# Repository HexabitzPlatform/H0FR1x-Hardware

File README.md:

# H0FR1x-Hardware
Hexabitz 230V/10A(RMS) SPDT Relay Module Hardware Design

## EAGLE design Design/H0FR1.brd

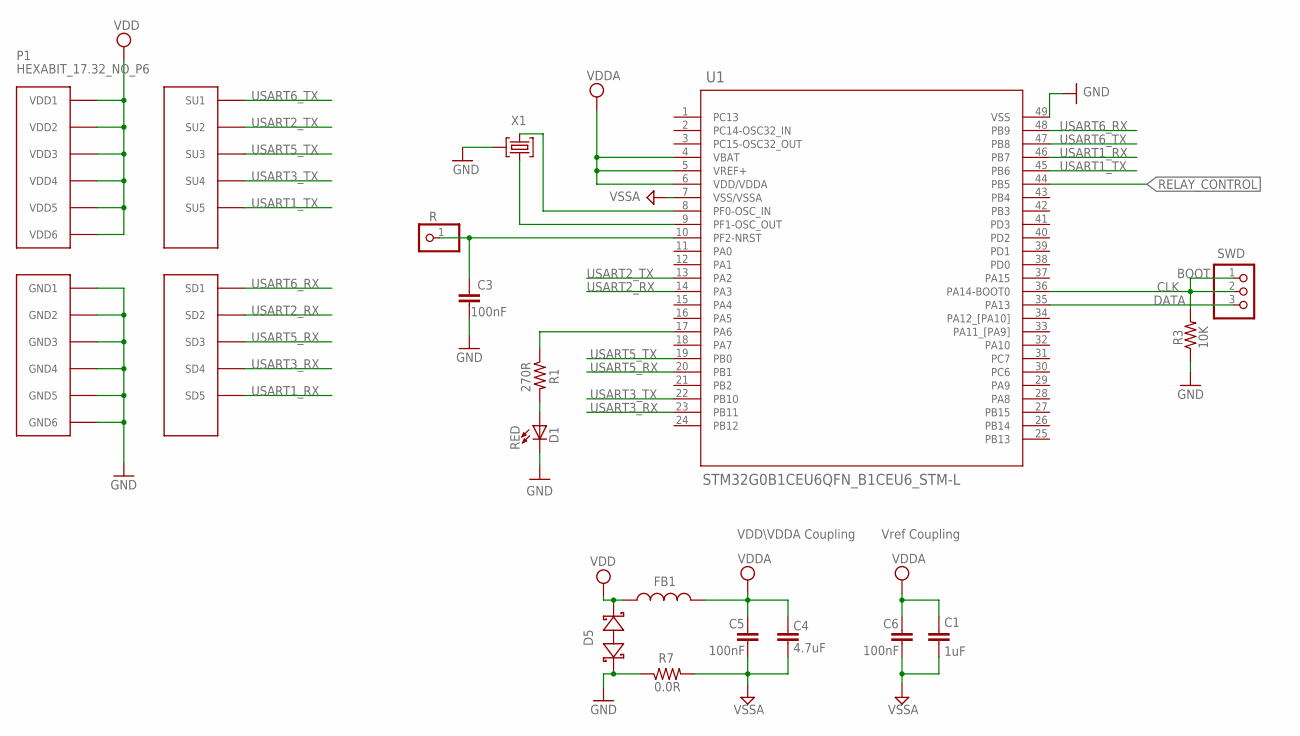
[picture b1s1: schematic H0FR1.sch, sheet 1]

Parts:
C1: 1uF; C-0805
C3, C5, C6: 100nF; C-0603
C4: 4.7uF; C-0805
D1: RED; VLMS1300-GS08; MPN VLMS1300-GS08
D5: BOURNS_CDSOD323-T03SCBOURNS_CDSOD323-T03SC_0_0; BOURNS_CDSOD323-T03SC_0
FB1: FB-TDK_MMZ1608Y300B; FB-0603; MPN MMZ1608Y300B
P1: HEXABIT_17.32_NO_P6
R: R; 1X01
R1: 270R; R-0603
R3: 10K; R-0603
R7: 0.0R; R-0603; MPN RC0603JR-070RL
SWD: PINHD-1X3; 1X03
TRIMBLE-LOGO1: HEXA-LOGO
U1: STM32G0B1CEU6QFN_B1CEU6_STM-L; QFN_B1CEU6_STM-L
X1: XTALL_CSTCE8M00G52

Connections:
CLK: R3.2, SWD.1, SWD.2, U1.36 (PA14-BOOT0)
DATA: SWD.3, U1.35 (PA13)
GND: C3.2, D1.C, D5.1 (A), P1.PAD_PD7 (GND1), P1.PAD_PD8 (GND2), P1.PAD_PD9 (GND3), P1.PAD_PD10 (GND4), P1.PAD_PD11 (GND5), P1.PAD_PD12 (GND6), R3.1, R7.1, U1.49 (VSS), X1.P$2 (2); also elsewhere on the board
unnamed: D1.A, R1.2
unnamed: R1.1, U1.17 (PA6)
unnamed: C3.1, R.1, U1.10 (PF2-NRST)
unnamed: U1.9 (PF1-OSC_OUT), X1.P$1 (1)
unnamed: U1.8 (PF0-OSC_IN), X1.P$3 (3)
RELAY_CONTROL: U1.44 (PB5); also elsewhere on the board
USART1_RX: P1.PAD_PD5 (SD5), U1.46 (PB7)
USART1_TX: P1.PAD_PU5 (SU5), U1.45 (PB6)
USART2_RX: P1.PAD_PD2 (SD2), U1.14 (PA3)
USART2_TX: P1.PAD_PU2 (SU2), U1.13 (PA2)
USART3_RX: P1.PAD_PD4 (SD4), U1.23 (PB11)
USART3_TX: P1.PAD_PU4 (SU4), U1.22 (PB10)
USART5_RX: P1.PAD_PD3 (SD3), U1.20 (PB1)
USART5_TX: P1.PAD_PU3 (SU3), U1.19 (PB0)
USART6_RX: P1.PAD_PD1 (SD1), U1.48 (PB9)
USART6_TX: P1.PAD_PU1 (SU1), U1.47 (PB8)
VDD: D5.2 (C), FB1.2, P1.PAD_PU7 (VDD1), P1.PAD_PU8 (VDD2), P1.PAD_PU9 (VDD3), P1.PAD_PU10 (VDD4), P1.PAD_PU11 (VDD5), P1.PAD_PU12 (VDD6); also elsewhere on the board
VDDA: C1.1, C4.1, C5.1, C6.1, FB1.1, U1.4 (VBAT), U1.5 (VREF+), U1.6 (VDD/VDDA)
VSSA: C1.2, C4.2, C5.2, C6.2, R7.2, U1.7 (VSS/VSSA)

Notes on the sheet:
Vref Coupling
VDD\VDDA Coupling
BOOT

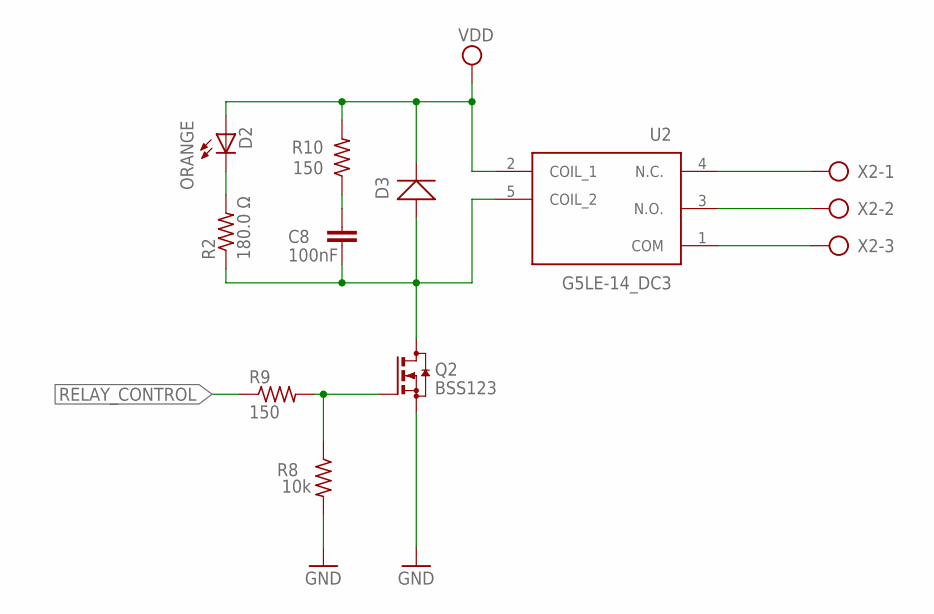
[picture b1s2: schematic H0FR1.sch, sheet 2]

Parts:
C8: 100nF; C-0603; TOLERANCE 10%; VOLTAGE_RATING 10V; MPN C0603C104K8RACTU
D2: orange; VLMS1300-GS08; MPN VLMY1300-GS08
D3: 40V 300MA; SOD-323
Q2: BSS123; SOT23
R2: 180.0 Ω; R-0603; TOLERANCE ±5%; MPN ERJ-3GEYJ181V
R8: 10k; R-0603; TOLERANCE 5%; MPN RC0603JR-07680KL
R9: 150; R-0603; TOLERANCE ±5%; MPN CRCW06031K00JNEA
R10: 150; R-0603; TOLERANCE 5%; MPN RC0603JR-07680KL
U2: G5LE-14_DC3; G5LE-14_SPDT
X2: AK300/3

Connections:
COM: U2.1 (COM), X2.3
GND: Q2.2 (S), R8.2; also elsewhere on the board
unnamed: C8.2, D3.+, Q2.3 (D), R2.1, U2.5 (COIL_2)
unnamed: D2.C, R2.2
unnamed: Q2.1 (G), R8.1, R9.2
unnamed: C8.1, R10.1
NC: U2.4 (N.C.), X2.1
NO: U2.3 (N.O.), X2.2
RELAY_CONTROL: R9.1; also elsewhere on the board
VDD: D2.A, D3.-, R10.2, U2.2 (COIL_1); also elsewhere on the board

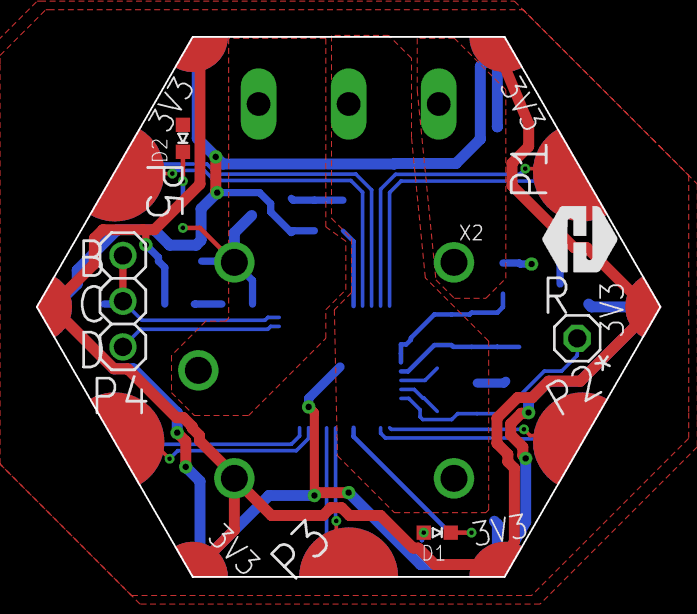
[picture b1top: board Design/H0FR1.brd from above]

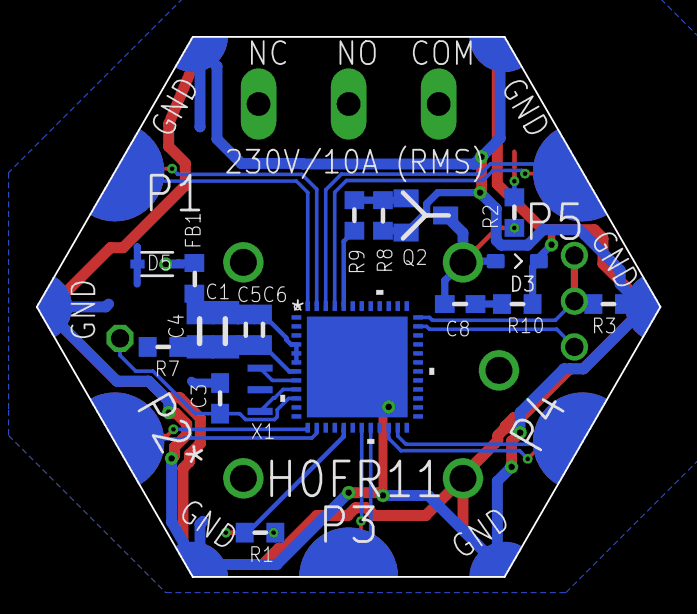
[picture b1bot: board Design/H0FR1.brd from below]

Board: 2 copper layers, 34.6 x 30.0 mm, 27 parts (19 on the bottom side), 29 nets.

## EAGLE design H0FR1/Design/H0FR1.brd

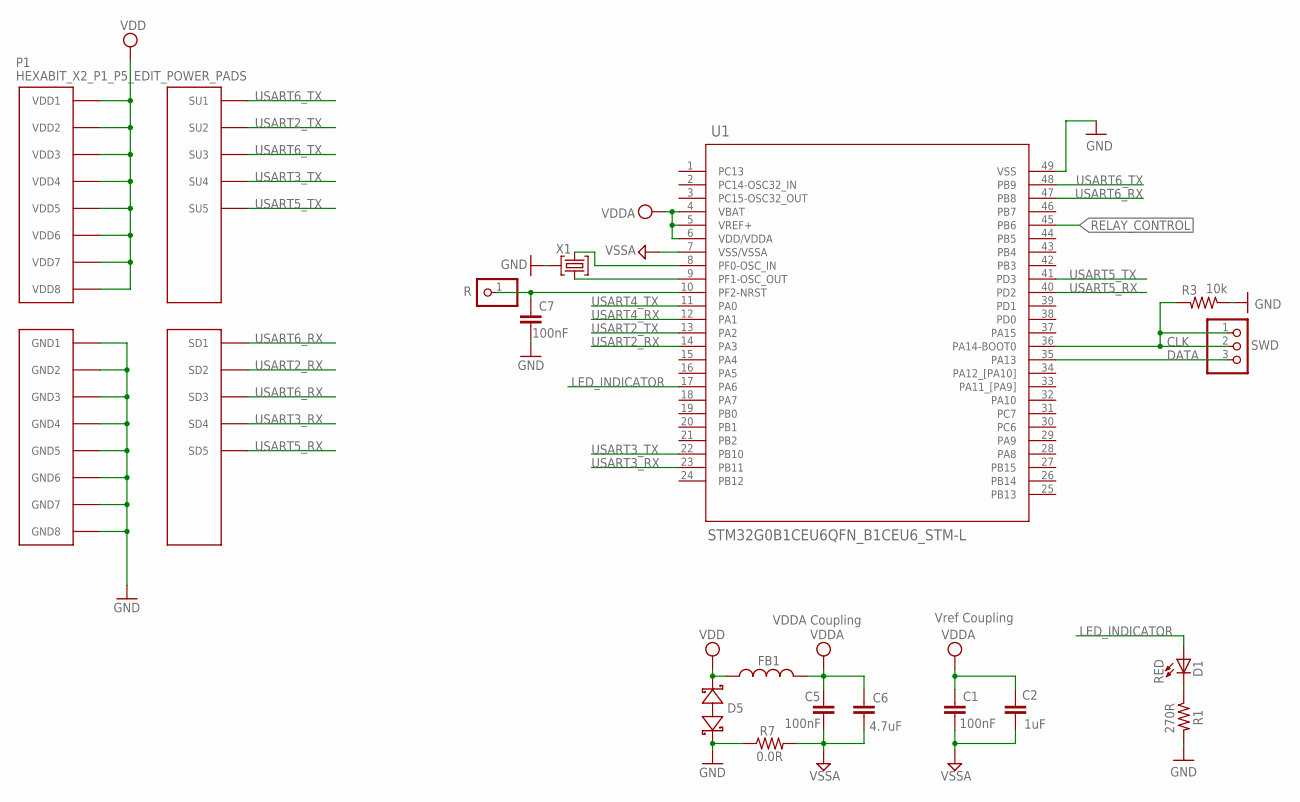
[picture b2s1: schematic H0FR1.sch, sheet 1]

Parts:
C1: 100nF; C-0603; TOLERANCE 10%; VOLTAGE_RATING 10V; MPN C0603C104K8RACTU
C2: 1uF; C-0805; TOLERANCE 10%; VOLTAGE_RATING 16V; MPN CC0805KKX7R7BB105
C5, C7: 100nF; C-0603
C6: 4.7uF; C-0805; TOLERANCE 10%; VOLTAGE_RATING 25V; MPN GRM21BC81E475KA12L
D1: RED; VLMS1300-GS08; MPN VLMS1300-GS08
D5: BOURNS_CDSOD323-T03SCBOURNS_CDSOD323-T03SC_0_0; BOURNS_CDSOD323-T03SC_0
FB1: FB-0603
P1: HEXABIT_X2_P1_P5_EDIT_POWER_PADS
R: R; 1X01
R1: 270R; R-0603
R3: 10k; R-0603; TOLERANCE 5%; MPN RC0603JR-0710KL
R7: 0.0R; R-0603
SWD: PINHD-1X3SWD; SWD
TRIMBLE-LOGO2: HEXA-LOGO
U1: STM32G0B1CEU6QFN_B1CEU6_STM-L; QFN_B1CEU6_STM-L
X1: XTALL_CSTCE8M00G52

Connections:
CLK: R3.2, SWD.1, SWD.2, U1.36 (PA14-BOOT0)
DATA: SWD.3, U1.35 (PA13)
GND: C7.2, D5.2 (C), P1.PAD_PD11 (GND1), P1.PAD_PD12 (GND2), P1.PAD_PD13 (GND3), P1.PAD_PD14 (GND4), P1.PAD_PD17 (GND5), P1.PAD_PD18 (GND6), P1.PAD_PD19 (GND7), P1.PAD_PD20 (GND8), R1.2, R3.1, R7.1, U1.49 (VSS), X1.P$2 (2); also elsewhere on the board
LED_INDICATOR: D1.A, U1.17 (PA6)
unnamed: D1.C, R1.1
unnamed: C7.1, R.1, U1.10 (PF2-NRST)
unnamed: U1.9 (PF1-OSC_OUT), X1.P$1 (1)
unnamed: U1.8 (PF0-OSC_IN), X1.P$3 (3)
RELAY_CONTROL: U1.45 (PB6); also elsewhere on the board
USART2_RX: P1.PAD_PD2 (SD2), U1.14 (PA3)
USART2_TX: P1.PAD_PU2 (SU2), U1.13 (PA2)
USART3_RX: P1.PAD_PD4 (SD4), U1.23 (PB11)
USART3_TX: P1.PAD_PU4 (SU4), U1.22 (PB10)
USART4_RX: U1.12 (PA1)
USART4_TX: U1.11 (PA0)
USART5_RX: P1.PAD_PD5 (SD5), U1.40 (PD2)
USART5_TX: P1.PAD_PU5 (SU5), U1.41 (PD3)
USART6_RX: P1.PAD_PD1 (SD1), P1.PAD_PD3 (SD3), U1.47 (PB8)
USART6_TX: P1.PAD_PU1 (SU1), P1.PAD_PU3 (SU3), U1.48 (PB9)
VDD: D5.1 (A), FB1.1, P1.PAD_PU11 (VDD1), P1.PAD_PU12 (VDD2), P1.PAD_PU13 (VDD3), P1.PAD_PU14 (VDD4), P1.PAD_PU17 (VDD5), P1.PAD_PU18 (VDD6), P1.PAD_PU19 (VDD7), P1.PAD_PU20 (VDD8); also elsewhere on the board
VDDA: C1.1, C2.1, C5.1, C6.1, FB1.2, U1.4 (VBAT), U1.5 (VREF+), U1.6 (VDD/VDDA)
VSSA: C1.2, C2.2, C5.2, C6.2, R7.2, U1.7 (VSS/VSSA)

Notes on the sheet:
Vref Coupling
VDDA Coupling

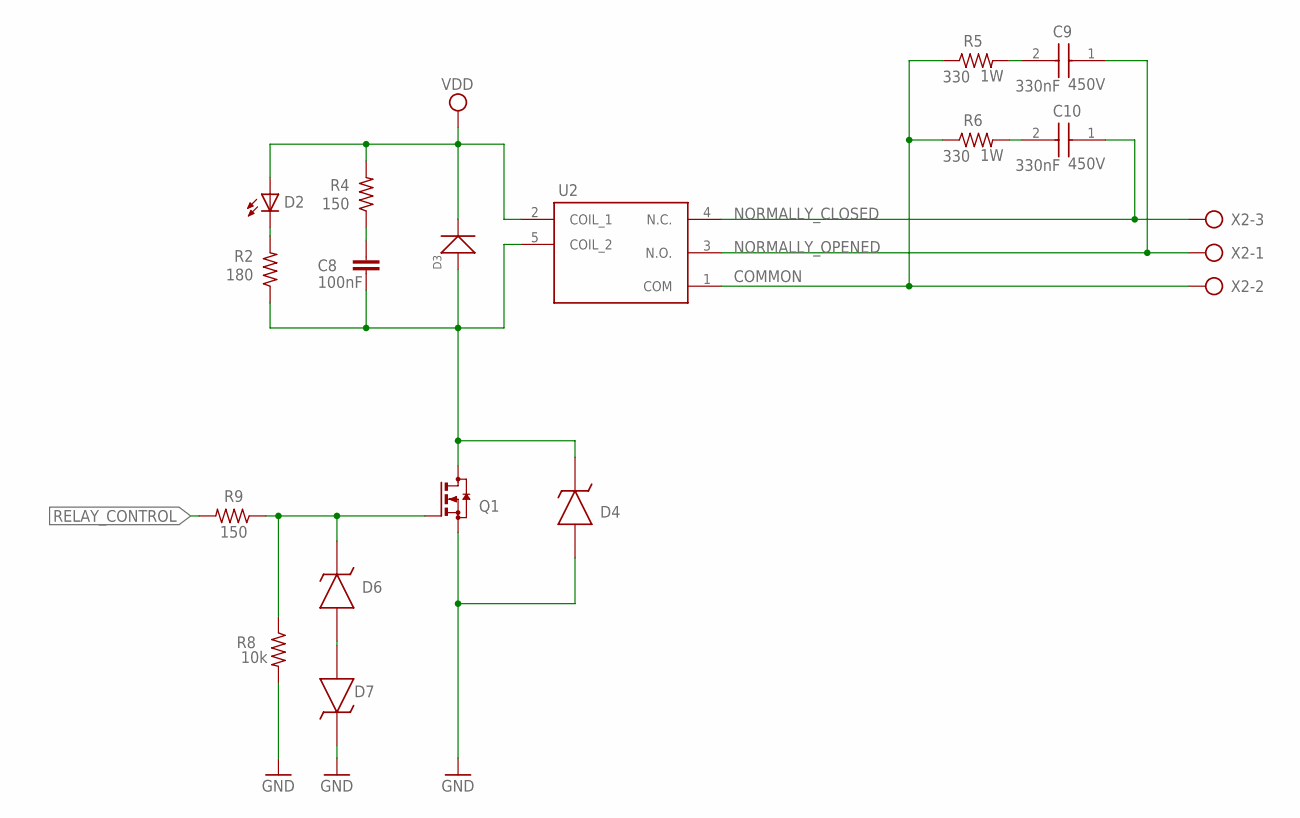
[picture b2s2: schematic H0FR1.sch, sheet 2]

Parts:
C8: 100nF; C-0603; TOLERANCE 10%; VOLTAGE_RATING 10V; MPN C0603C104K8RACTU
C9, C10: 330nF; B32922Q_(18_X_8.5)
D2: RED; VLMS1300-GS08; MPN VLMY1300-GS08
D3: 40V 300MA; SOD-323
D4, D6, D7: MMSZ4705T1GMMSZ4705T1G; DIO_MMSZ4700T1G
Q1: BSS123; SOT23
R2: 180; R-0603; TOLERANCE ±5%; MPN ERJ-3GEYJ181V
R4, R9: 150; R-0603; TOLERANCE 5%; MPN RC0603JR-07680KL
R5, R6: 330; R2512; MPN RMCF2512JT330R
R8: 10k; R-0603; TOLERANCE 5%; MPN RC0603JR-07680KL
U2: G5LE-14_DC3; G5LE-14_SPDT
X2: AK300/3

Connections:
COMMON: R5.1, R6.1, U2.1 (COM), X2.2
GND: D4.A, D7.K, Q1.2 (S), R8.2; also elsewhere on the board
unnamed: D6.A, D7.A
unnamed: D6.K, Q1.1 (G), R8.1, R9.1
unnamed: D2.C, R2.2
unnamed: C9.2, R5.2
unnamed: C8.1, R4.1
unnamed: C10.2, R6.2
unnamed: C8.2, D3.+, D4.K, Q1.3 (D), R2.1, U2.5 (COIL_2)
NORMALLY_CLOSED: C10.1, U2.4 (N.C.), X2.3
NORMALLY_OPENED: C9.1, U2.3 (N.O.), X2.1
RELAY_CONTROL: R9.2; also elsewhere on the board
VDD: D2.A, D3.-, R4.2, U2.2 (COIL_1); also elsewhere on the board

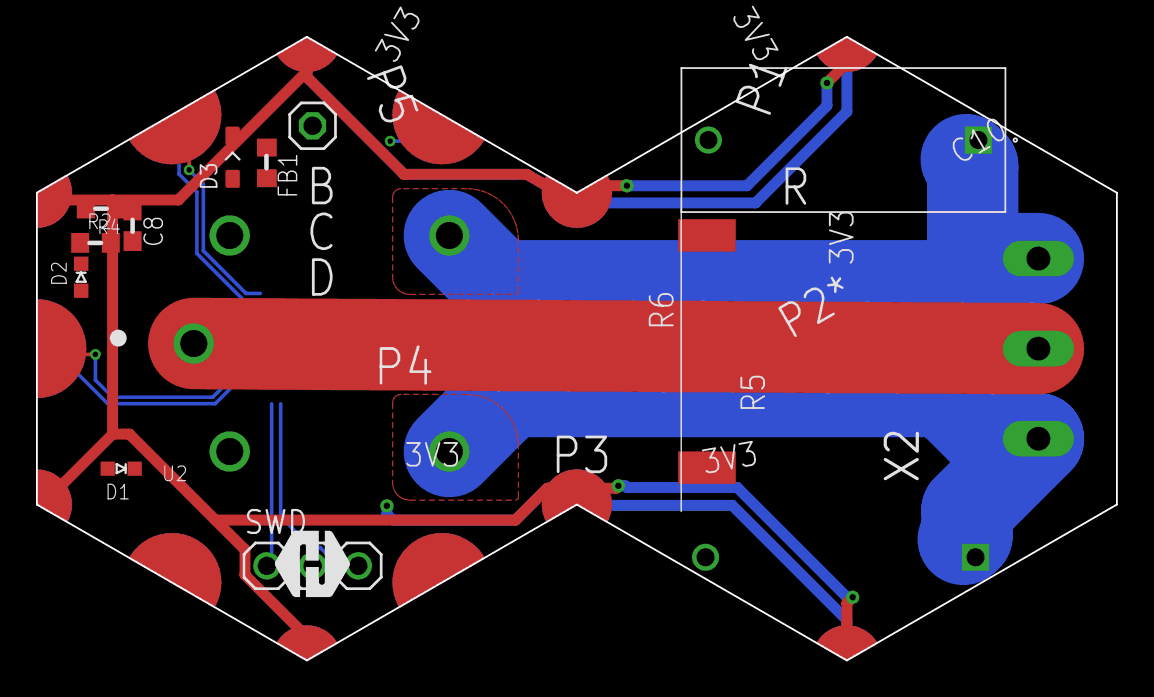
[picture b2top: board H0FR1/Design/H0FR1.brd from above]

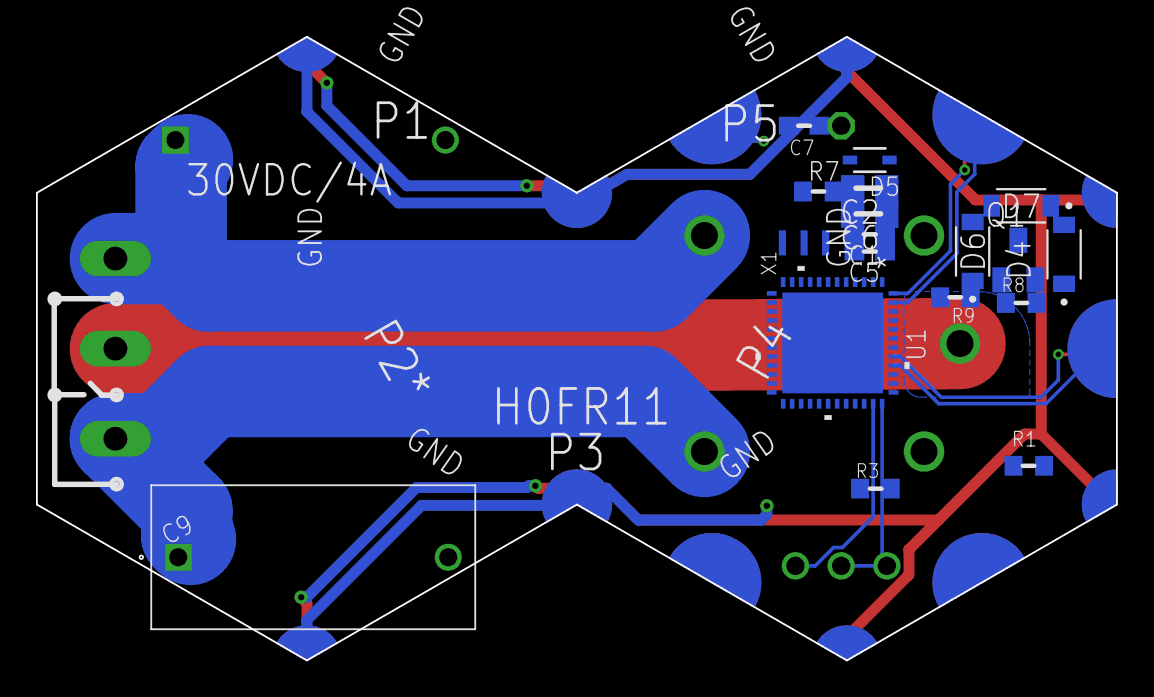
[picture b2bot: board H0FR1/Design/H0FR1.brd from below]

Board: 2 copper layers, 60.0 x 34.6 mm, 34 parts (18 on the bottom side), 30 nets.

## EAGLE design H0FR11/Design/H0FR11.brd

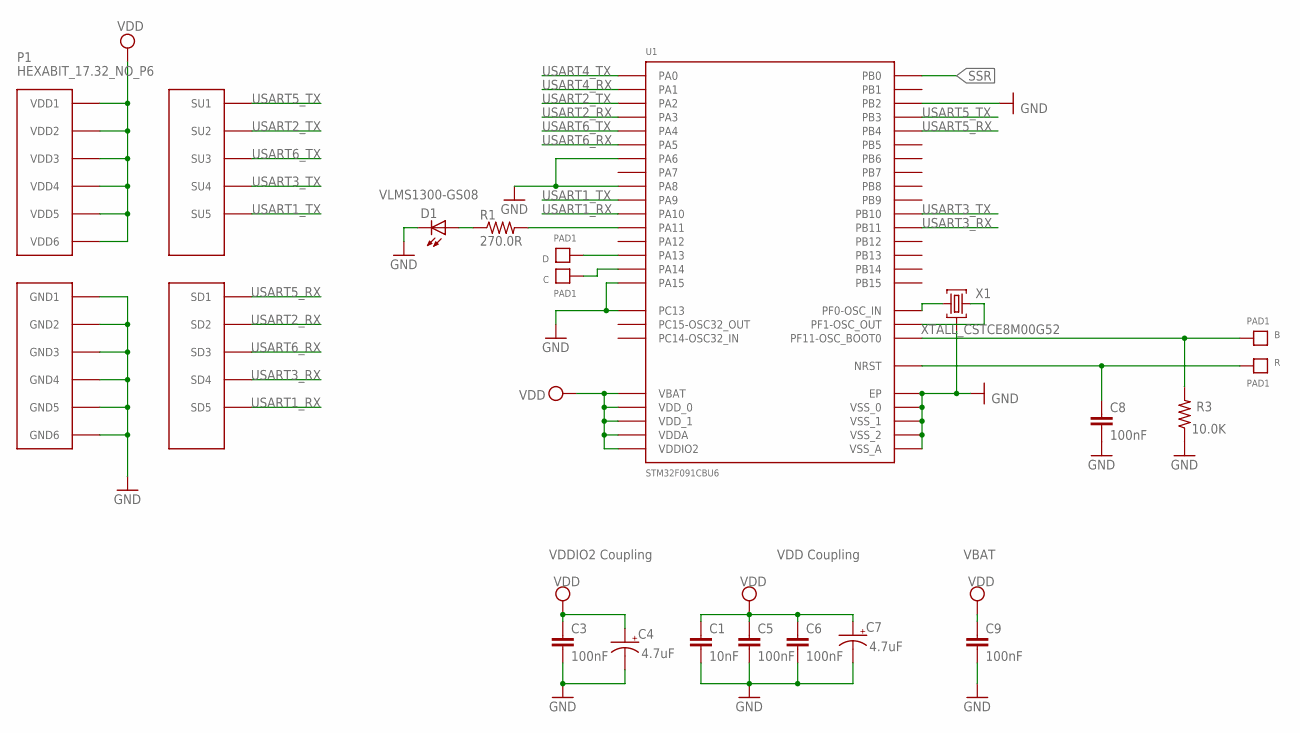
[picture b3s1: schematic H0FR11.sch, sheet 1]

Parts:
B: PAD1
C: PAD1
C1: 10nF; C-0603; TOLERANCE 10%; VOLTAGE_RATING 50V; MPN C0603C103K5RACTU
C3, C6, C8: 100nF; C-0603; TOLERANCE 10%; VOLTAGE_RATING 10V; MPN C0603C104K8RACTU
C4, C7: 4.7uF; C-0805-POL; TOLERANCE 10%; VOLTAGE_RATING 25V; MPN GRM21BC81E475KA12L
C5: 100nF; C-0603; TOLERANCE 10%; VOLTAGE_RATING 10; MPN C0603C104K8RACTU
C9: 100nF; C-0603; TOLERANCE 10V; VOLTAGE_RATING 10%; MPN C0603C104K8RACTU
D: PAD1
D1: VLMS1300-GS08; MPN VLMS1300-GS08
P1: HEXABIT_17.32_NO_P6
R: PAD1
R1: 270.0R; R-0603; TOLERANCE 1%; MPN RC0603FR-07270RL
R3: 10.0K; R-0603; TOLERANCE 5%; MPN RC0603JR-0710KL
U1: STM32F091CBU6
X1: XTALL_CSTCE8M00G52

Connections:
B1: B.P$1, B.P$2, R3.2, U1.P$44 (PF11-OSC_BOOT0)
GND: C1.2, C3.2, C4.2 (-), C5.2, C6.2, C7.2 (-), C8.2, C9.2, D1.C, P1.PAD_PD7 (GND1), P1.PAD_PD8 (GND2), P1.PAD_PD9 (GND3), P1.PAD_PD10 (GND4), P1.PAD_PD11 (GND5), P1.PAD_PD12 (GND6), R3.1, U1.EP, U1.P$2 (PC13), U1.P$8 (VSS_A), U1.P$16 (PA6), U1.P$20 (PB2), U1.P$23 (VSS_0), U1.P$29 (PA8), U1.P$35 (VSS_1), U1.P$38 (PA15), U1.P$47 (VSS_2), X1.P$2 (2); also elsewhere on the board
unnamed: R1.2, U1.P$32 (PA11)
unnamed: D1.A, R1.1
unnamed: U1.P$5 (PF0-OSC_IN), X1.P$1 (1)
unnamed: U1.P$6 (PF1-OSC_OUT), X1.P$3 (3)
unnamed: D.P$1, D.P$2, U1.P$34 (PA13)
unnamed: C.P$1, C.P$2, U1.P$37 (PA14)
R1: C8.1, R.P$1, R.P$2, U1.P$7 (NRST)
SSR: U1.P$18 (PB0); also elsewhere on the board
USART1_RX: P1.PAD_PD5 (SD5), U1.P$31 (PA10)
USART1_TX: P1.PAD_PU5 (SU5), U1.P$30 (PA9)
USART2_RX: P1.PAD_PD2 (SD2), U1.P$13 (PA3)
USART2_TX: P1.PAD_PU2 (SU2), U1.P$12 (PA2)
USART3_RX: P1.PAD_PD4 (SD4), U1.P$22 (PB11)
USART3_TX: P1.PAD_PU4 (SU4), U1.P$21 (PB10)
USART4_RX: U1.P$11 (PA1)
USART4_TX: U1.P$10 (PA0)
USART5_RX: P1.PAD_PD1 (SD1), U1.P$40 (PB4)
USART5_TX: P1.PAD_PU1 (SU1), U1.P$39 (PB3)
USART6_RX: P1.PAD_PD3 (SD3), U1.P$15 (PA5)
USART6_TX: P1.PAD_PU3 (SU3), U1.P$14 (PA4)
VDD: C1.1, C3.1, C4.1 (+), C5.1, C6.1, C7.1 (+), C9.1, P1.PAD_PU7 (VDD1), P1.PAD_PU8 (VDD2), P1.PAD_PU9 (VDD3), P1.PAD_PU10 (VDD4), P1.PAD_PU11 (VDD5), P1.PAD_PU12 (VDD6), U1.P$1 (VBAT), U1.P$9 (VDDA), U1.P$24 (VDD_0), U1.P$36 (VDDIO2), U1.P$48 (VDD_1); also elsewhere on the board

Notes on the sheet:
VDDIO2 Coupling
VDD Coupling
VBAT

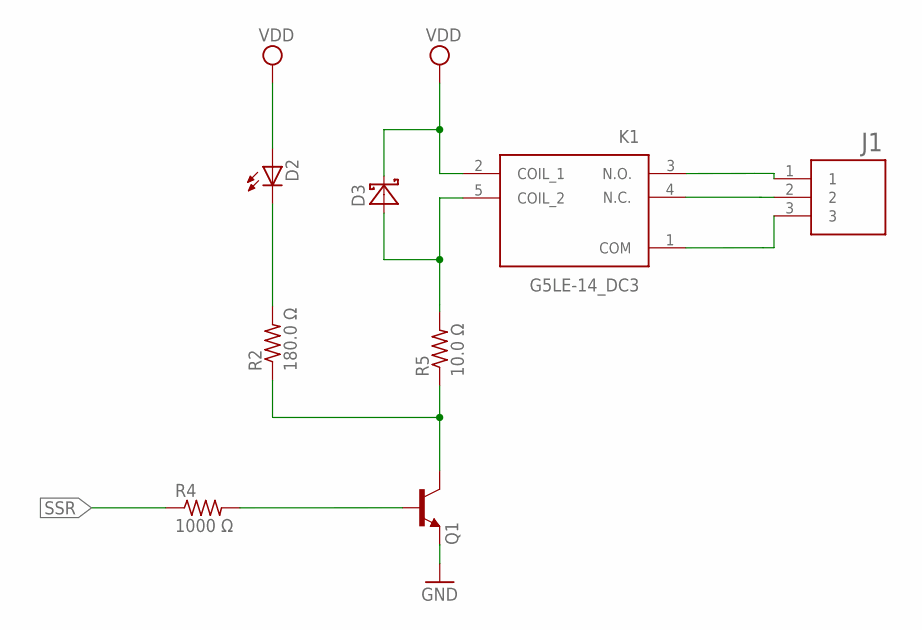
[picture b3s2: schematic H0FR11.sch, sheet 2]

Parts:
D2: VLMS1300-GS08; MPN VLMY1300-GS08
D3: SMD-DIODE-SCHOTTKY-40V-300MA(SOD-323); SOD-323
J1: CON-PHOENIX-350_1755749; SHDR3W100P0X508_1X3_1724X860X1
K1: G5LE-14_DC3; G5LE-14_SPDT
Q1: MMBT3904LT1; VOLTAGE_RATING_DC 40.0 V; MPN MMBT3904LT1G
R2: 180.0 Ω; R-0603; TOLERANCE ±5%; MPN ERJ-3GEYJ181V
R4: 1000 Ω; R-0603; TOLERANCE ±5%; MPN CRCW06031K00JNEA
R5: 10.0 Ω; R-0603; TOLERANCE ±1%; MPN CRCW060310R0FKEB

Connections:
GND: Q1.2 (E); also elsewhere on the board
unnamed: D3.+ (A), K1.5 (COIL_2), R5.2
unnamed: J1.1, K1.3 (N.O.)
unnamed: D2.C, R2.2
unnamed: Q1.1 (B), R4.2
unnamed: J1.2, K1.4 (N.C.)
unnamed: J1.3, K1.1 (COM)
unnamed: Q1.3 (C), R2.1, R5.1
SSR: R4.1; also elsewhere on the board
VDD: D2.A, D3.- (C), K1.2 (COIL_1); also elsewhere on the board

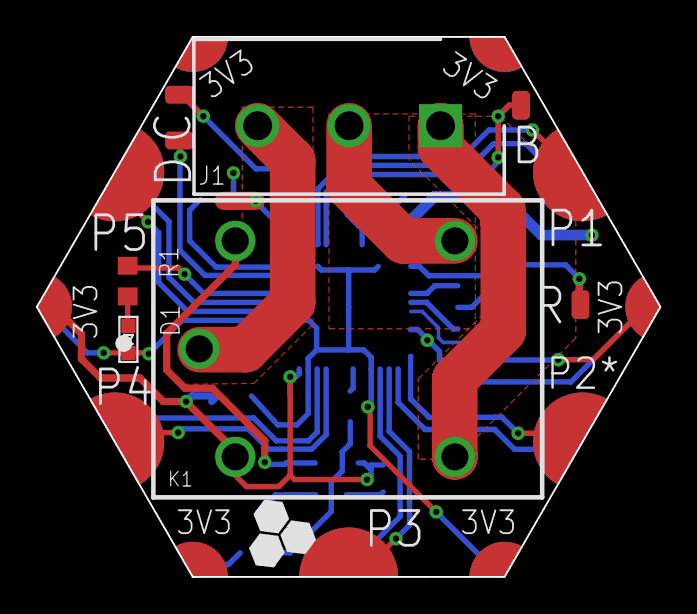
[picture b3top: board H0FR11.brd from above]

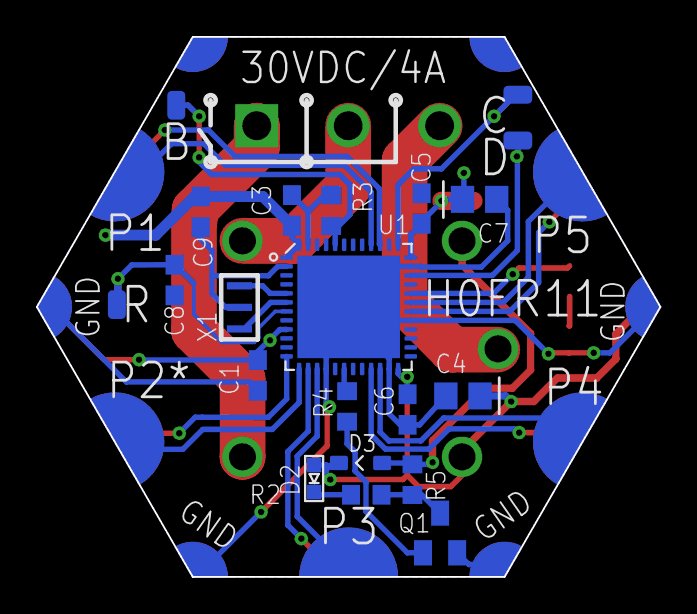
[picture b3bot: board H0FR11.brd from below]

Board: 2 copper layers, 34.6 x 30.0 mm, 26 parts (17 on the bottom side), 28 nets.

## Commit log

2019-06-02 Adding design and release rev 0 files
2019-06-05 Adding git ignore
    Moving files into folder
2019-07-01 Fixed R2 PN
2019-08-06 Update H0FR10.xlsx
    Update & fix some BOM entries
2020-04-08 editing notes & descriptions (3oz to 2oz & 10A to 8A)
2020-06-10 change base resistor(R4) from 2k4 to 1k0 Schematic & BOM was changed
2020-06-15 Fix ERC errors Generate PDF Release at V0 again
2021-04-27 - Changed to Rev1; this revision is 1OZ /4AMP..
2024-03-10 Not finished yet.... -Changing the MCU to STM32G0B1CEU6N -Improving the layout design
2024-05-30 Design modification
2024-05-31 Schematic modification
2024-06-01 Edit the decription
2024-06-21 Intial parts placing on the board
2024-07-19 All finish, reviewed version
2024-09-10 -Fixing an issue on the silkscreen layer

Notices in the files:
parts and their libraries:
COPYRIGHT: Copyright (C) 2021 Ultra Librarian. All rights reserved.
